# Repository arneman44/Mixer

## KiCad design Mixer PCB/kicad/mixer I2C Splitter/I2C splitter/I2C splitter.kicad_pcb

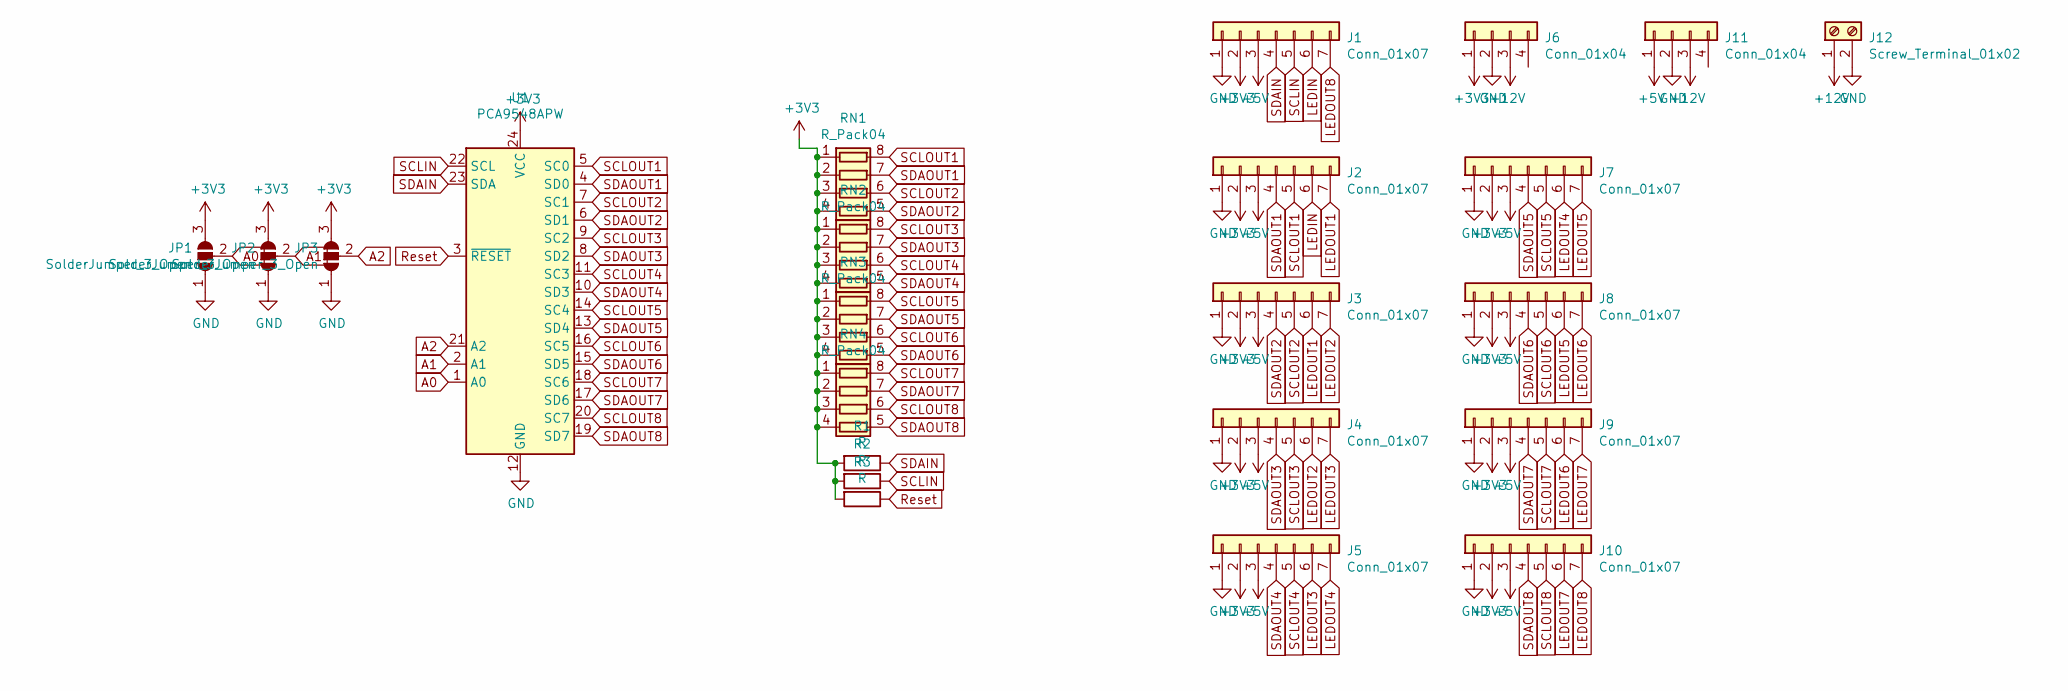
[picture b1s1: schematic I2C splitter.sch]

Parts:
J1, J2, J3, J4, J5, J7, J8, J9, J10: Conn_01x07; PinSocket_1x07_P2.54mm_Vertical
J6, J11: Conn_01x04; PinSocket_1x04_P2.54mm_Vertical
J12: Screw_Terminal_01x02; TerminalBlock_bornier-2_P5.08mm
JP1, JP2, JP3: SolderJumper_3_Open; SolderJumper-3_P1.3mm_Open_RoundedPad1.0x1.5mm
R1, R2, R3: R; R_0805_2012Metric_Pad1.15x1.40mm_HandSolder
RN1, RN2, RN3, RN4: R_Pack04; R_Array_Convex_4x0603
U1: PCA9548APW; TSSOP-24_4.4x7.8mm_P0.65mm

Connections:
+3V3: J1.2, J2.2, J3.2, J4.2, J5.2, J6.1, J7.2, J8.2, J9.2, J10.2, JP1.3 (B), JP2.3 (B), JP3.3 (B), R1.2, R2.2, R3.2, RN1.1 (R1.1), RN1.2 (R2.1), RN1.3 (R3.1), RN1.4 (R4.1), RN2.1 (R1.1), RN2.2 (R2.1), RN2.3 (R3.1), RN2.4 (R4.1), RN3.1 (R1.1), RN3.2 (R2.1), RN3.3 (R3.1), RN3.4 (R4.1), RN4.1 (R1.1), RN4.2 (R2.1), RN4.3 (R3.1), RN4.4 (R4.1), U1.24 (VCC)
+5V: J1.3, J2.3, J3.3, J4.3, J5.3, J7.3, J8.3, J9.3, J10.3, J11.1
+12V: J6.3, J11.3, J12.1
A0: JP1.2 (C), U1.1 (A0)
A1: JP2.2 (C), U1.2 (A1)
A2: JP3.2 (C), U1.21 (A2)
GND: J1.1, J2.1, J3.1, J4.1, J5.1, J6.2, J7.1, J8.1, J9.1, J10.1, J11.2, J12.2, JP1.1 (A), JP2.1 (A), JP3.1 (A), U1.12 (GND)
LEDIN: J1.6, J2.6
LEDOUT1: J2.7, J3.6
LEDOUT2: J3.7, J4.6
LEDOUT3: J4.7, J5.6
LEDOUT4: J5.7, J7.6
LEDOUT5: J7.7, J8.6
LEDOUT6: J8.7, J9.6
LEDOUT7: J9.7, J10.6
LEDOUT8: J1.7, J10.7
Reset: R3.1, U1.3 (~RESET)
SCLIN: J1.5, R2.1, U1.22 (SCL)
SCLOUT1: J2.5, RN1.8 (R1.2), U1.5 (SC0)
SCLOUT2: J3.5, RN1.6 (R3.2), U1.7 (SC1)
SCLOUT3: J4.5, RN2.8 (R1.2), U1.9 (SC2)
SCLOUT4: J5.5, RN2.6 (R3.2), U1.11 (SC3)
SCLOUT5: J7.5, RN3.8 (R1.2), U1.14 (SC4)
SCLOUT6: J8.5, RN3.6 (R3.2), U1.16 (SC5)
SCLOUT7: J9.5, RN4.8 (R1.2), U1.18 (SC6)
SCLOUT8: J10.5, RN4.6 (R3.2), U1.20 (SC7)
SDAIN: J1.4, R1.1, U1.23 (SDA)
SDAOUT1: J2.4, RN1.7 (R2.2), U1.4 (SD0)
SDAOUT2: J3.4, RN1.5 (R4.2), U1.6 (SD1)
SDAOUT3: J4.4, RN2.7 (R2.2), U1.8 (SD2)
SDAOUT4: J5.4, RN2.5 (R4.2), U1.10 (SD3)
SDAOUT5: J7.4, RN3.7 (R2.2), U1.13 (SD4)
SDAOUT6: J8.4, RN3.5 (R4.2), U1.15 (SD5)
SDAOUT7: J9.4, RN4.7 (R2.2), U1.17 (SD6)
SDAOUT8: J10.4, RN4.5 (R4.2), U1.19 (SD7)

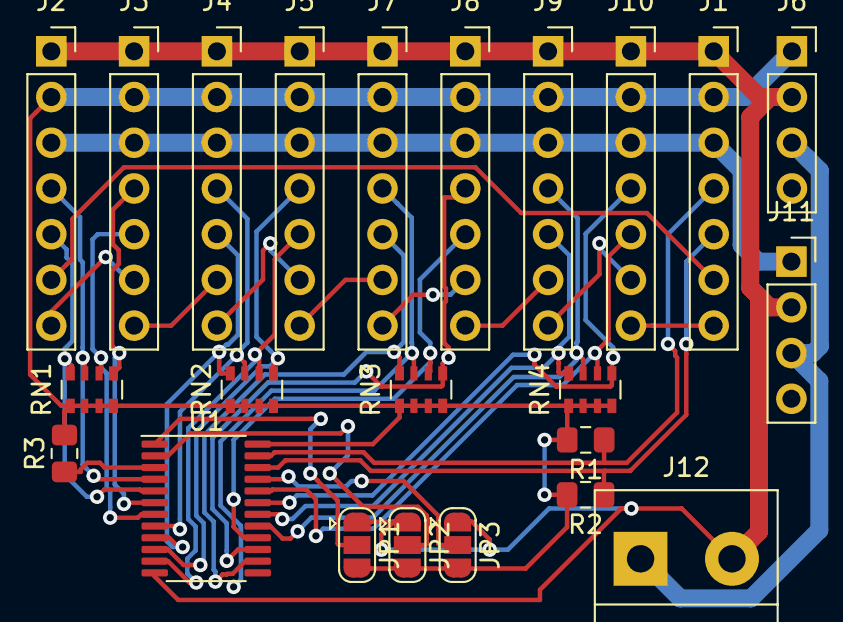
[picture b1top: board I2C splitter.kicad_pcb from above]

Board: 2 copper layers, 23 parts (0 on the bottom side), 35 nets.

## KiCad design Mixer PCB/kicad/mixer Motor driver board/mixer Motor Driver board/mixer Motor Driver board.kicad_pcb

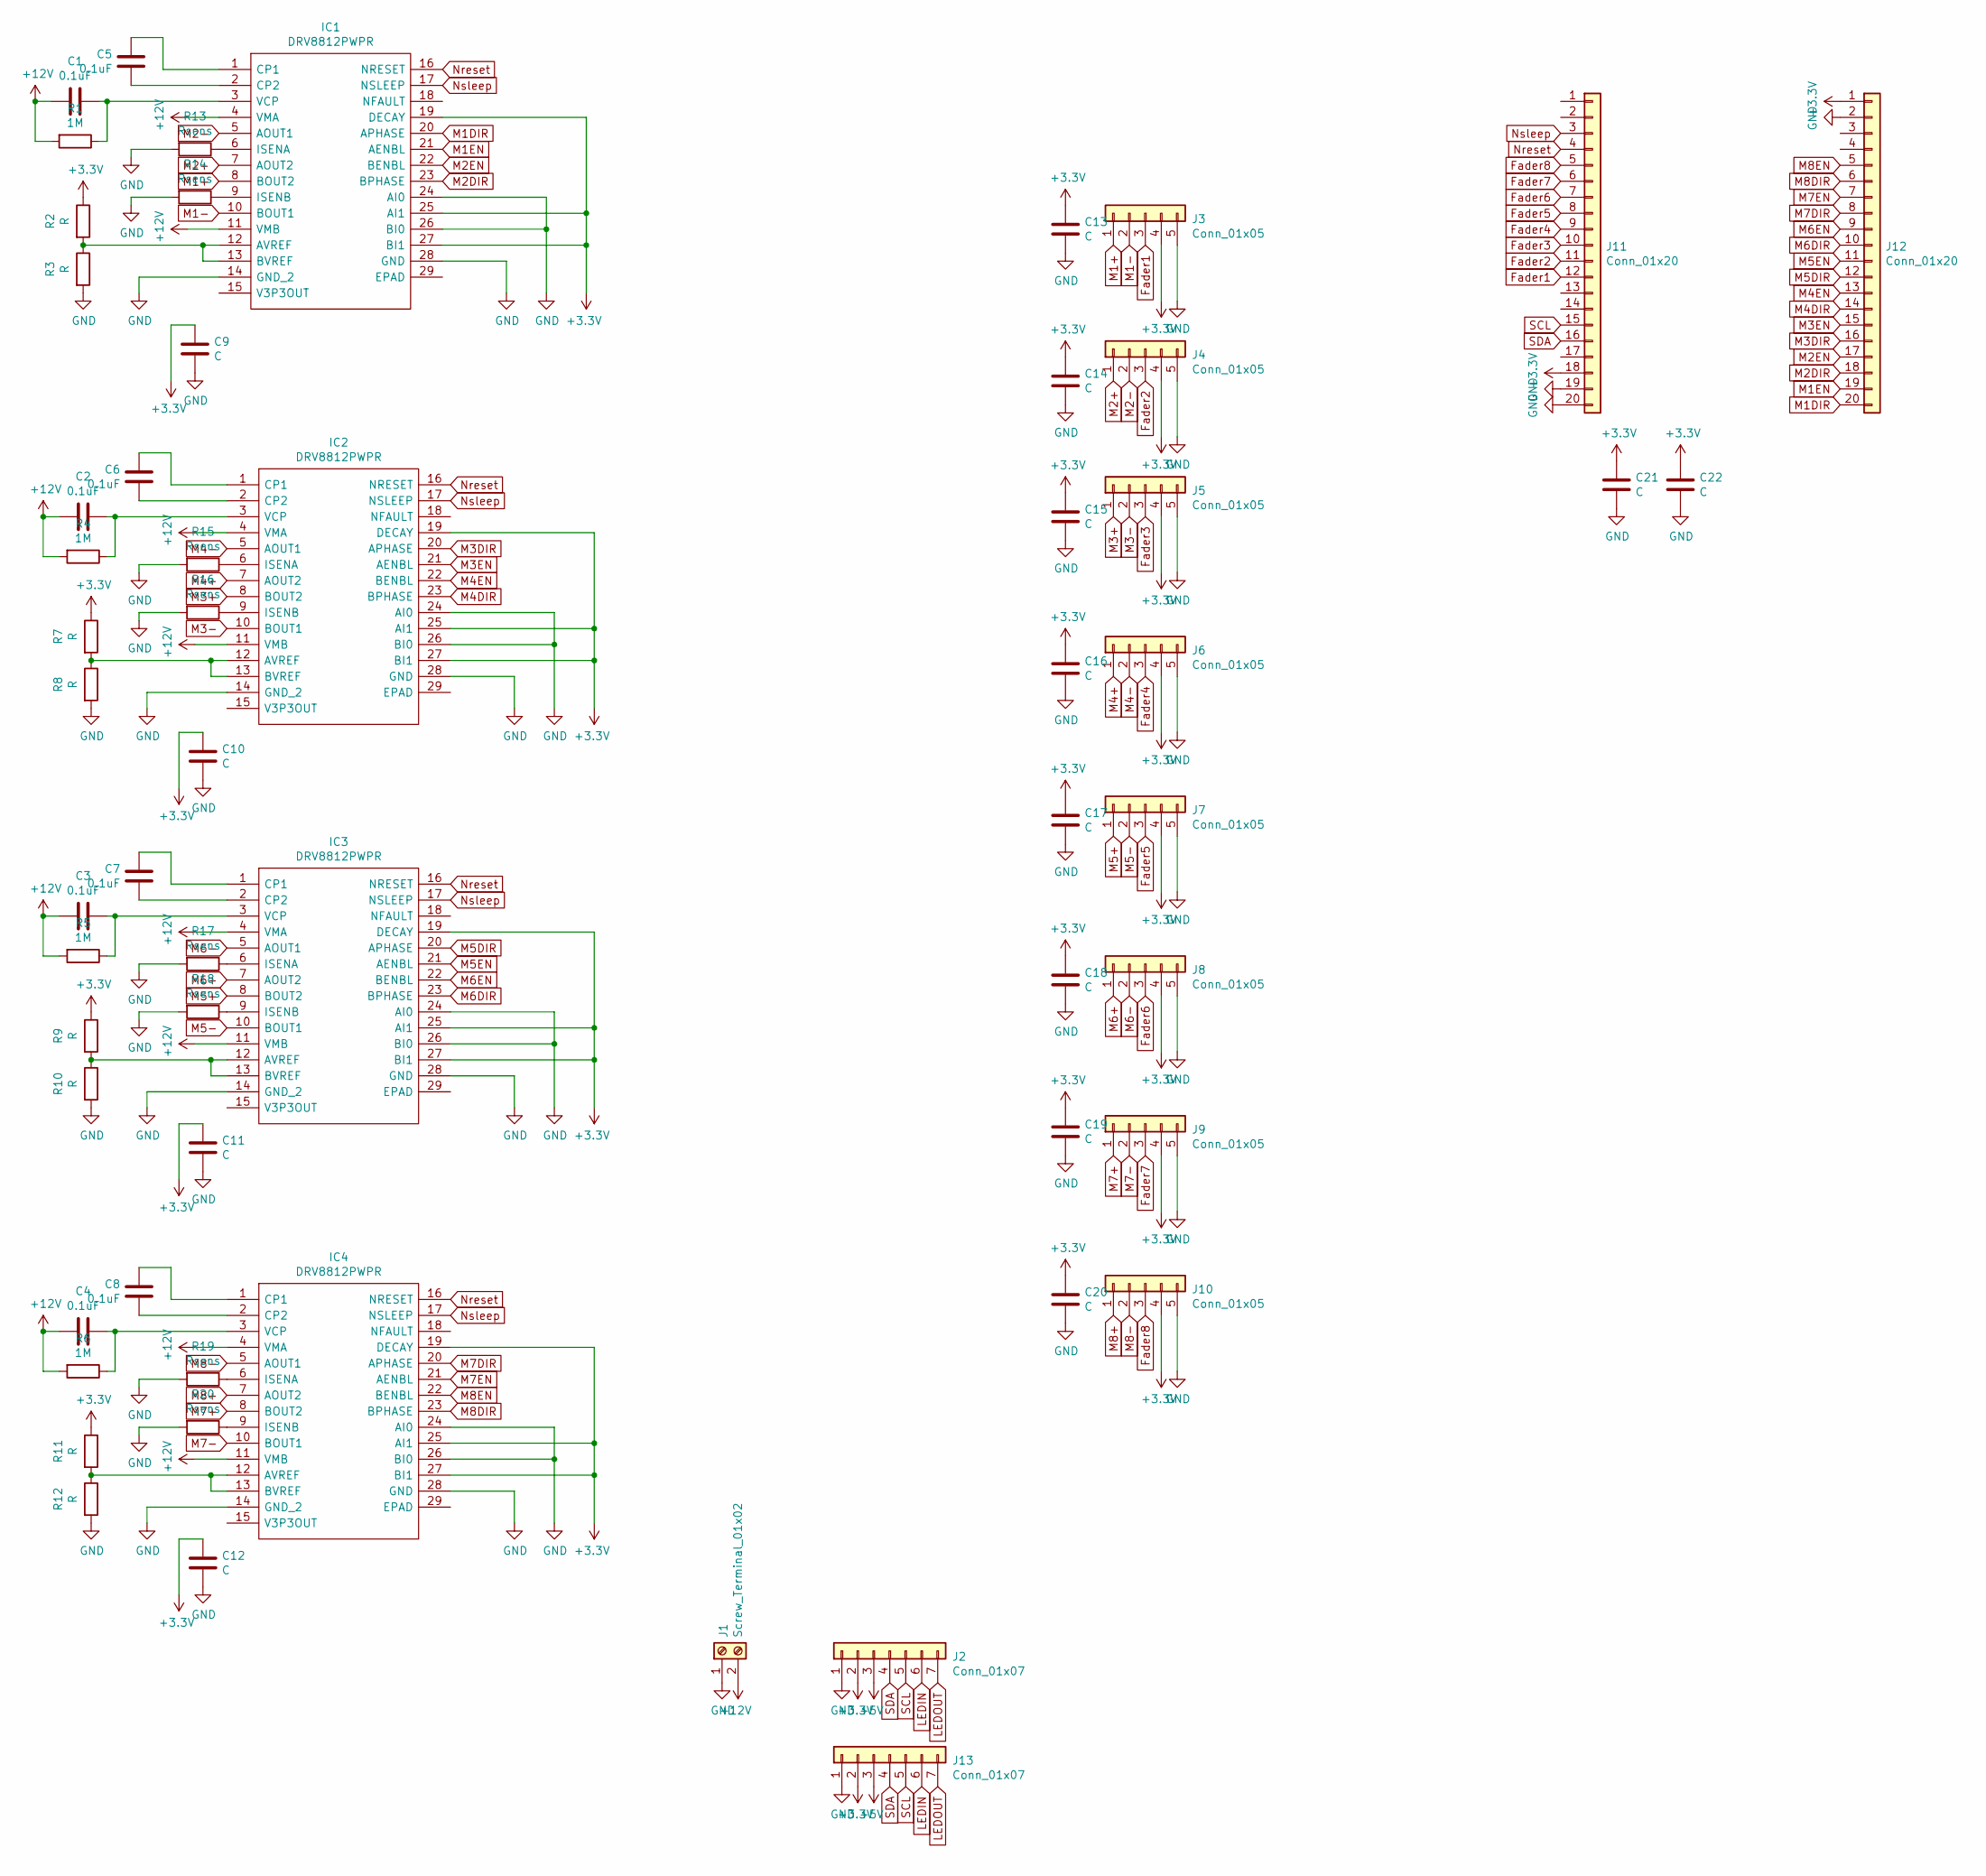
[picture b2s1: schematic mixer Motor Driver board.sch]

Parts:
C1, C2, C3, C4, C5, C6, C7, C8: 0.1uF; C_0805_2012Metric_Pad1.15x1.40mm_HandSolder
C9, C10, C11, C12, C13, C14, C15, C16, C17, C18, C19, C20, C21, C22: C; C_0805_2012Metric_Pad1.15x1.40mm_HandSolder
IC1, IC2, IC3, IC4: DRV8812PWPR; SOP65P640X120-29N; Manufacturer_Part_Number DRV8812PWPR; Mouser Part Number 595-DRV8812PWPR
J1: Screw_Terminal_01x02; TerminalBlock_bornier-2_P5.08mm
J2, J13: Conn_01x07; PinSocket_1x07_P2.54mm_Vertical
J3, J4, J5, J6, J7, J8, J9, J10: Conn_01x05; PinSocket_1x05_P2.54mm_Vertical
J11, J12: Conn_01x20; PinSocket_1x20_P2.54mm_Vertical
R1, R4, R5, R6: 1M; R_0805_2012Metric_Pad1.15x1.40mm_HandSolder
R2, R3, R7, R8, R9, R10, R11, R12: R; R_0805_2012Metric_Pad1.15x1.40mm_HandSolder
R13, R14, R15, R16, R17, R18, R19, R20: Rsens; R_1206_3216Metric_Pad1.42x1.75mm_HandSolder

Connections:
+3V3: C9.1, C10.1, C11.1, C12.1, C13.1, C14.1, C15.1, C16.1, C17.1, C18.1, C19.1, C20.1, C21.1, C22.1, IC1.19 (DECAY), IC1.25 (AI1), IC1.27 (BI1), IC2.19 (DECAY), IC2.25 (AI1), IC2.27 (BI1), IC3.19 (DECAY), IC3.25 (AI1), IC3.27 (BI1), IC4.19 (DECAY), IC4.25 (AI1), IC4.27 (BI1), J2.2, J3.4, J4.4, J5.4, J6.4, J7.4, J8.4, J9.4, J10.4, J11.18, J12.1, J13.2, R2.1, R7.1, R9.1, R11.1
+5V: J2.3, J13.3
+12V: C1.2, C2.2, C3.2, C4.2, IC1.4 (VMA), IC1.11 (VMB), IC2.4 (VMA), IC2.11 (VMB), IC3.4 (VMA), IC3.11 (VMB), IC4.4 (VMA), IC4.11 (VMB), J1.2, R1.2, R4.2, R5.2, R6.2
Fader1: J3.3, J11.12
Fader2: J4.3, J11.11
Fader3: J5.3, J11.10
Fader4: J6.3, J11.9
Fader5: J7.3, J11.8
Fader6: J8.3, J11.7
Fader7: J9.3, J11.6
Fader8: J10.3, J11.5
GND: C9.2, C10.2, C11.2, C12.2, C13.2, C14.2, C15.2, C16.2, C17.2, C18.2, C19.2, C20.2, C21.2, C22.2, IC1.14 (GND_2), IC1.24 (AI0), IC1.26 (BI0), IC1.28 (GND), IC2.14 (GND_2), IC2.24 (AI0), IC2.26 (BI0), IC2.28 (GND), IC3.14 (GND_2), IC3.24 (AI0), IC3.26 (BI0), IC3.28 (GND), IC4.14 (GND_2), IC4.24 (AI0), IC4.26 (BI0), IC4.28 (GND), J1.1, J2.1, J3.5, J4.5, J5.5, J6.5, J7.5, J8.5, J9.5, J10.5, J11.19, J11.20, J12.2, J13.1, R3.2, R8.2, R10.2, R12.2, R13.2, R14.2, R15.2, R16.2, R17.2, R18.2, R19.2, R20.2
LEDIN: J2.6, J13.6
LEDOUT: J2.7, J13.7
M1+: IC1.8 (BOUT2), J3.1
M1-: IC1.10 (BOUT1), J3.2
M1DIR: IC1.20 (APHASE), J12.20
M1EN: IC1.21 (AENBL), J12.19
M2+: IC1.7 (AOUT2), J4.1
M2-: IC1.5 (AOUT1), J4.2
M2DIR: IC1.23 (BPHASE), J12.18
M2EN: IC1.22 (BENBL), J12.17
M3+: IC2.8 (BOUT2), J5.1
M3-: IC2.10 (BOUT1), J5.2
M3DIR: IC2.20 (APHASE), J12.16
M3EN: IC2.21 (AENBL), J12.15
M4+: IC2.7 (AOUT2), J6.1
M4-: IC2.5 (AOUT1), J6.2
M4DIR: IC2.23 (BPHASE), J12.14
M4EN: IC2.22 (BENBL), J12.13
M5+: IC3.8 (BOUT2), J7.1
M5-: IC3.10 (BOUT1), J7.2
M5DIR: IC3.20 (APHASE), J12.12
M5EN: IC3.21 (AENBL), J12.11
M6+: IC3.7 (AOUT2), J8.1
M6-: IC3.5 (AOUT1), J8.2
M6DIR: IC3.23 (BPHASE), J12.10
M6EN: IC3.22 (BENBL), J12.9
M7+: IC4.8 (BOUT2), J9.1
M7-: IC4.10 (BOUT1), J9.2
M7DIR: IC4.20 (APHASE), J12.8
M7EN: IC4.21 (AENBL), J12.7
M8+: IC4.7 (AOUT2), J10.1
M8-: IC4.5 (AOUT1), J10.2
M8DIR: IC4.23 (BPHASE), J12.6
M8EN: IC4.22 (BENBL), J12.5
unnamed: C1.1, IC1.3 (VCP), R1.1
unnamed: C2.1, IC2.3 (VCP), R4.1
unnamed: C3.1, IC3.3 (VCP), R5.1
unnamed: C4.1, IC4.3 (VCP), R6.1
unnamed: C5.1, IC1.2 (CP2)
unnamed: C5.2, IC1.1 (CP1)
unnamed: C6.1, IC2.2 (CP2)
unnamed: C6.2, IC2.1 (CP1)
unnamed: C7.1, IC3.2 (CP2)
unnamed: C7.2, IC3.1 (CP1)
unnamed: C8.1, IC4.2 (CP2)
unnamed: C8.2, IC4.1 (CP1)
unnamed: IC1.6 (ISENA), R13.1
unnamed: IC1.9 (ISENB), R14.1
unnamed: IC1.12 (AVREF), IC1.13 (BVREF), R2.2, R3.1
unnamed: IC2.6 (ISENA), R15.1
unnamed: IC2.9 (ISENB), R16.1
unnamed: IC2.12 (AVREF), IC2.13 (BVREF), R7.2, R8.1
unnamed: IC3.6 (ISENA), R17.1
unnamed: IC3.9 (ISENB), R18.1
unnamed: IC3.12 (AVREF), IC3.13 (BVREF), R9.2, R10.1
unnamed: IC4.6 (ISENA), R19.1
unnamed: IC4.9 (ISENB), R20.1
unnamed: IC4.12 (AVREF), IC4.13 (BVREF), R11.2, R12.1
Nreset: IC1.16 (NRESET), IC2.16 (NRESET), IC3.16 (NRESET), IC4.16 (NRESET), J11.4
Nsleep: IC1.17 (NSLEEP), IC2.17 (NSLEEP), IC3.17 (NSLEEP), IC4.17 (NSLEEP), J11.3
SCL: J2.5, J11.15, J13.5
SDA: J2.4, J11.16, J13.4

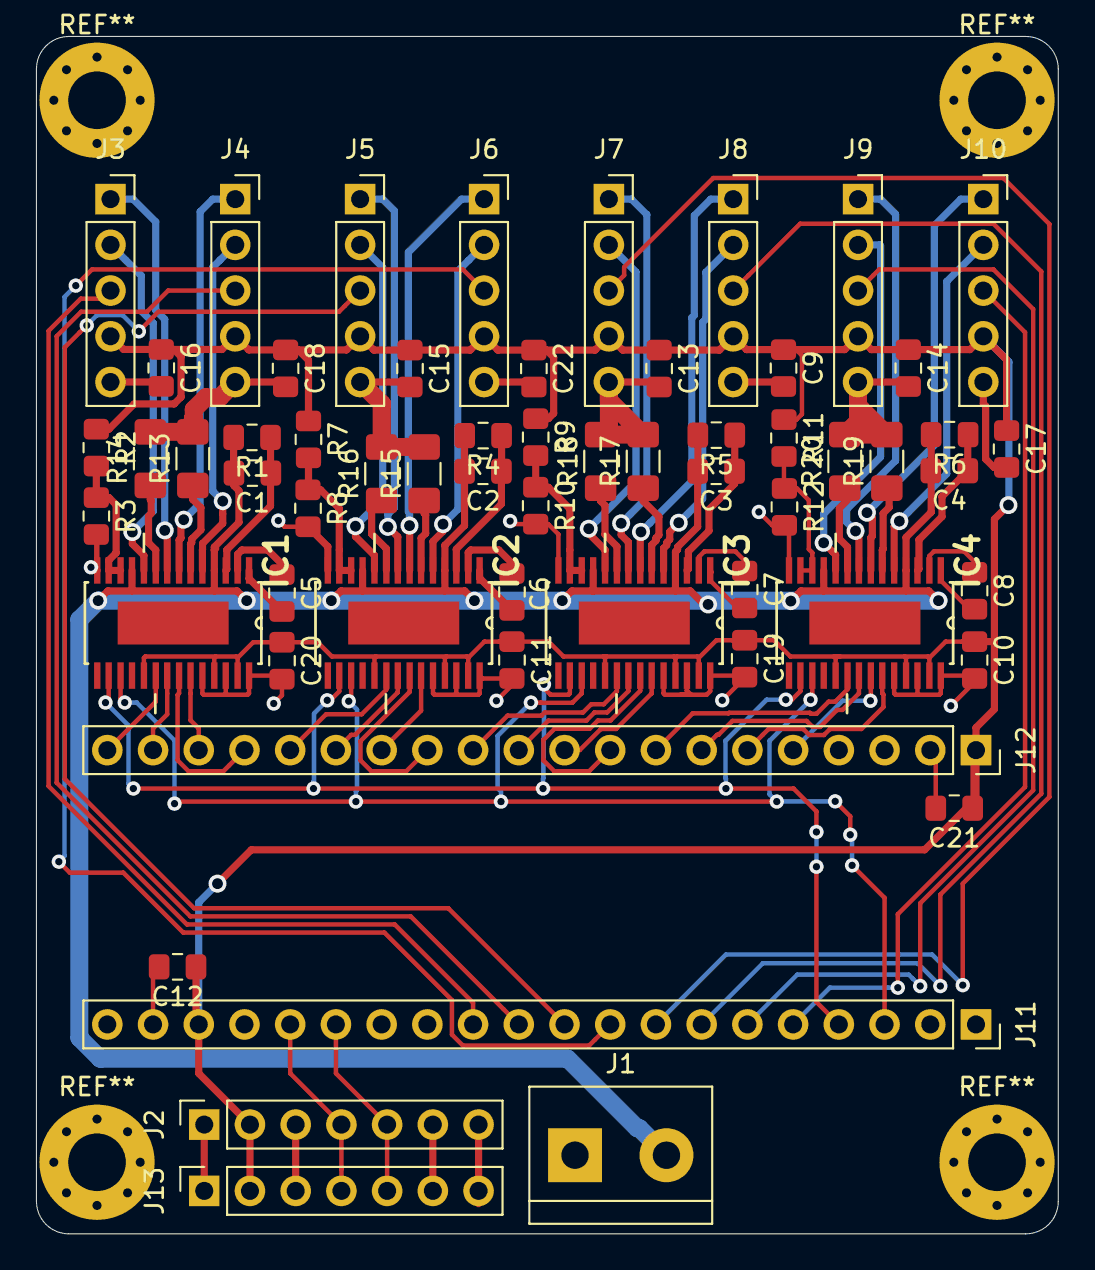
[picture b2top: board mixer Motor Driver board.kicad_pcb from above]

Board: 2 copper layers, 56.8 x 66.5 mm, 59 parts (0 on the bottom side), 74 nets.

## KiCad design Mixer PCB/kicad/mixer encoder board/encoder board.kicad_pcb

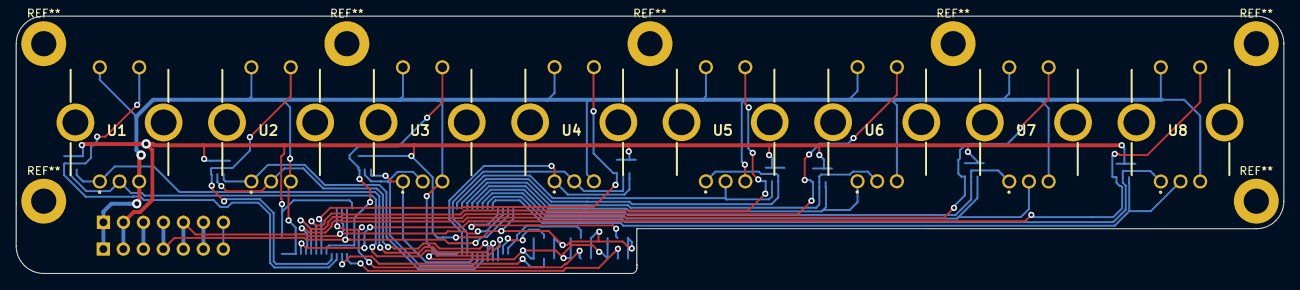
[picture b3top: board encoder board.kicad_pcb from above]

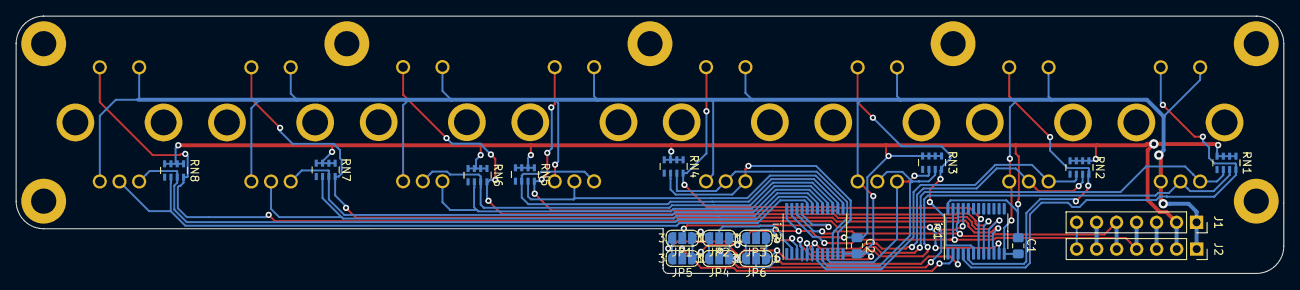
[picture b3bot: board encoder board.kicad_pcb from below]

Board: 2 copper layers, 161.0 x 32.7 mm, 28 parts (20 on the bottom side), 37 nets.

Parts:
C1, C2: C; C_0805_2012Metric_Pad1.15x1.40mm_HandSolder
J1, J2: Conn_01x07; PinSocket_1x07_P2.54mm_Vertical
JP1, JP2, JP3, JP4, JP5, JP6: SolderJumper_3_Open; SolderJumper-3_P1.3mm_Open_RoundedPad1.0x1.5mm_NumberLabels
RN1, RN2, RN3, RN4, RN5, RN6, RN7, RN8: R_Pack04; R_Array_Concave_4x0603
U1, U2, U3, U4, U5, U6, U7, U8: PEC11R-4015F-S0024; PEC12R-4XXXF-SXXXX_1
ic1, ic2: PCA9555; TSSOP-24_4.4x7.8mm_P0.65mm

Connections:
+3V3: C1.1, C2.1, J1.2, J2.2, JP1.3, JP2.3, JP3.3, JP4.3, JP5.3, JP6.3, RN1.1, RN1.2, RN1.3, RN1.4, RN2.1, RN2.2, RN2.3, RN2.4, RN3.1, RN3.2, RN3.3, RN3.4, RN4.1, RN4.2, RN4.3, RN4.4, RN5.1, RN5.2, RN5.3, RN5.4, RN6.1, RN6.2, RN6.3, RN6.4, RN7.1, RN7.2, RN7.3, RN7.4, RN8.1, RN8.2, RN8.3, RN8.4, ic1.24, ic2.24
+5V: J1.3, J2.3
A0_I2C1: JP4.2, ic1.21
A0_I2C2: JP1.2, ic2.21
A1_I2C1: JP5.2, ic1.2
A1_I2C2: JP2.2, ic2.2
A2_I2C1: JP6.2, ic1.3
A2_I2C2: JP3.2, ic2.3
Encoder1A: RN1.6, U1.1, ic2.5
Encoder1B: RN1.7, U1.3, ic2.4
Encoder1Button: RN1.8, U1.5, ic1.4
Encoder2A: RN2.6, U2.1, ic2.7
Encoder2B: RN2.7, U2.3, ic2.6
Encoder2Button: RN2.8, U2.5, ic1.5
Encoder3A: RN3.6, U3.1, ic2.9
Encoder3B: RN3.7, U3.3, ic2.8
Encoder3Button: RN3.8, U3.5, ic1.6
Encoder4A: RN4.6, U4.1, ic2.11
Encoder4B: RN4.7, U4.3, ic2.10
Encoder4Button: RN4.8, U4.5, ic1.7
Encoder5A: RN5.6, U5.1, ic2.14
Encoder5B: RN5.7, U5.3, ic2.13
Encoder5Button: RN5.8, U5.5, ic1.8
Encoder6A: RN6.6, U6.1, ic2.16
Encoder6B: RN6.7, U6.3, ic2.15
Encoder6Button: RN6.8, U6.5, ic1.9
Encoder7A: RN7.7, U7.1, ic2.17
Encoder7B: RN7.6, U7.3, ic2.18
Encoder7Button: RN7.8, U7.5, ic1.10
Encoder8A: RN8.7, U8.1, ic2.19
Encoder8B: RN8.6, U8.3, ic2.20
Encoder8Button: RN8.8, U8.5, ic1.11
GND: C1.2, C2.2, J1.1, J2.1, JP1.1, JP2.1, JP3.1, JP4.1, JP5.1, JP6.1, U1.2, U1.4, U2.2, U2.4, U3.2, U3.4, U4.2, U4.4, U5.2, U5.4, U6.2, U6.4, U7.2, U7.4, U8.2, U8.4, ic1.12, ic2.12
LEDIN: J1.6, J2.6
LEDOUT1: J1.7, J2.7
SCL: J1.5, J2.5, ic1.22, ic2.22
SDA: J1.4, J2.4, ic1.23, ic2.23

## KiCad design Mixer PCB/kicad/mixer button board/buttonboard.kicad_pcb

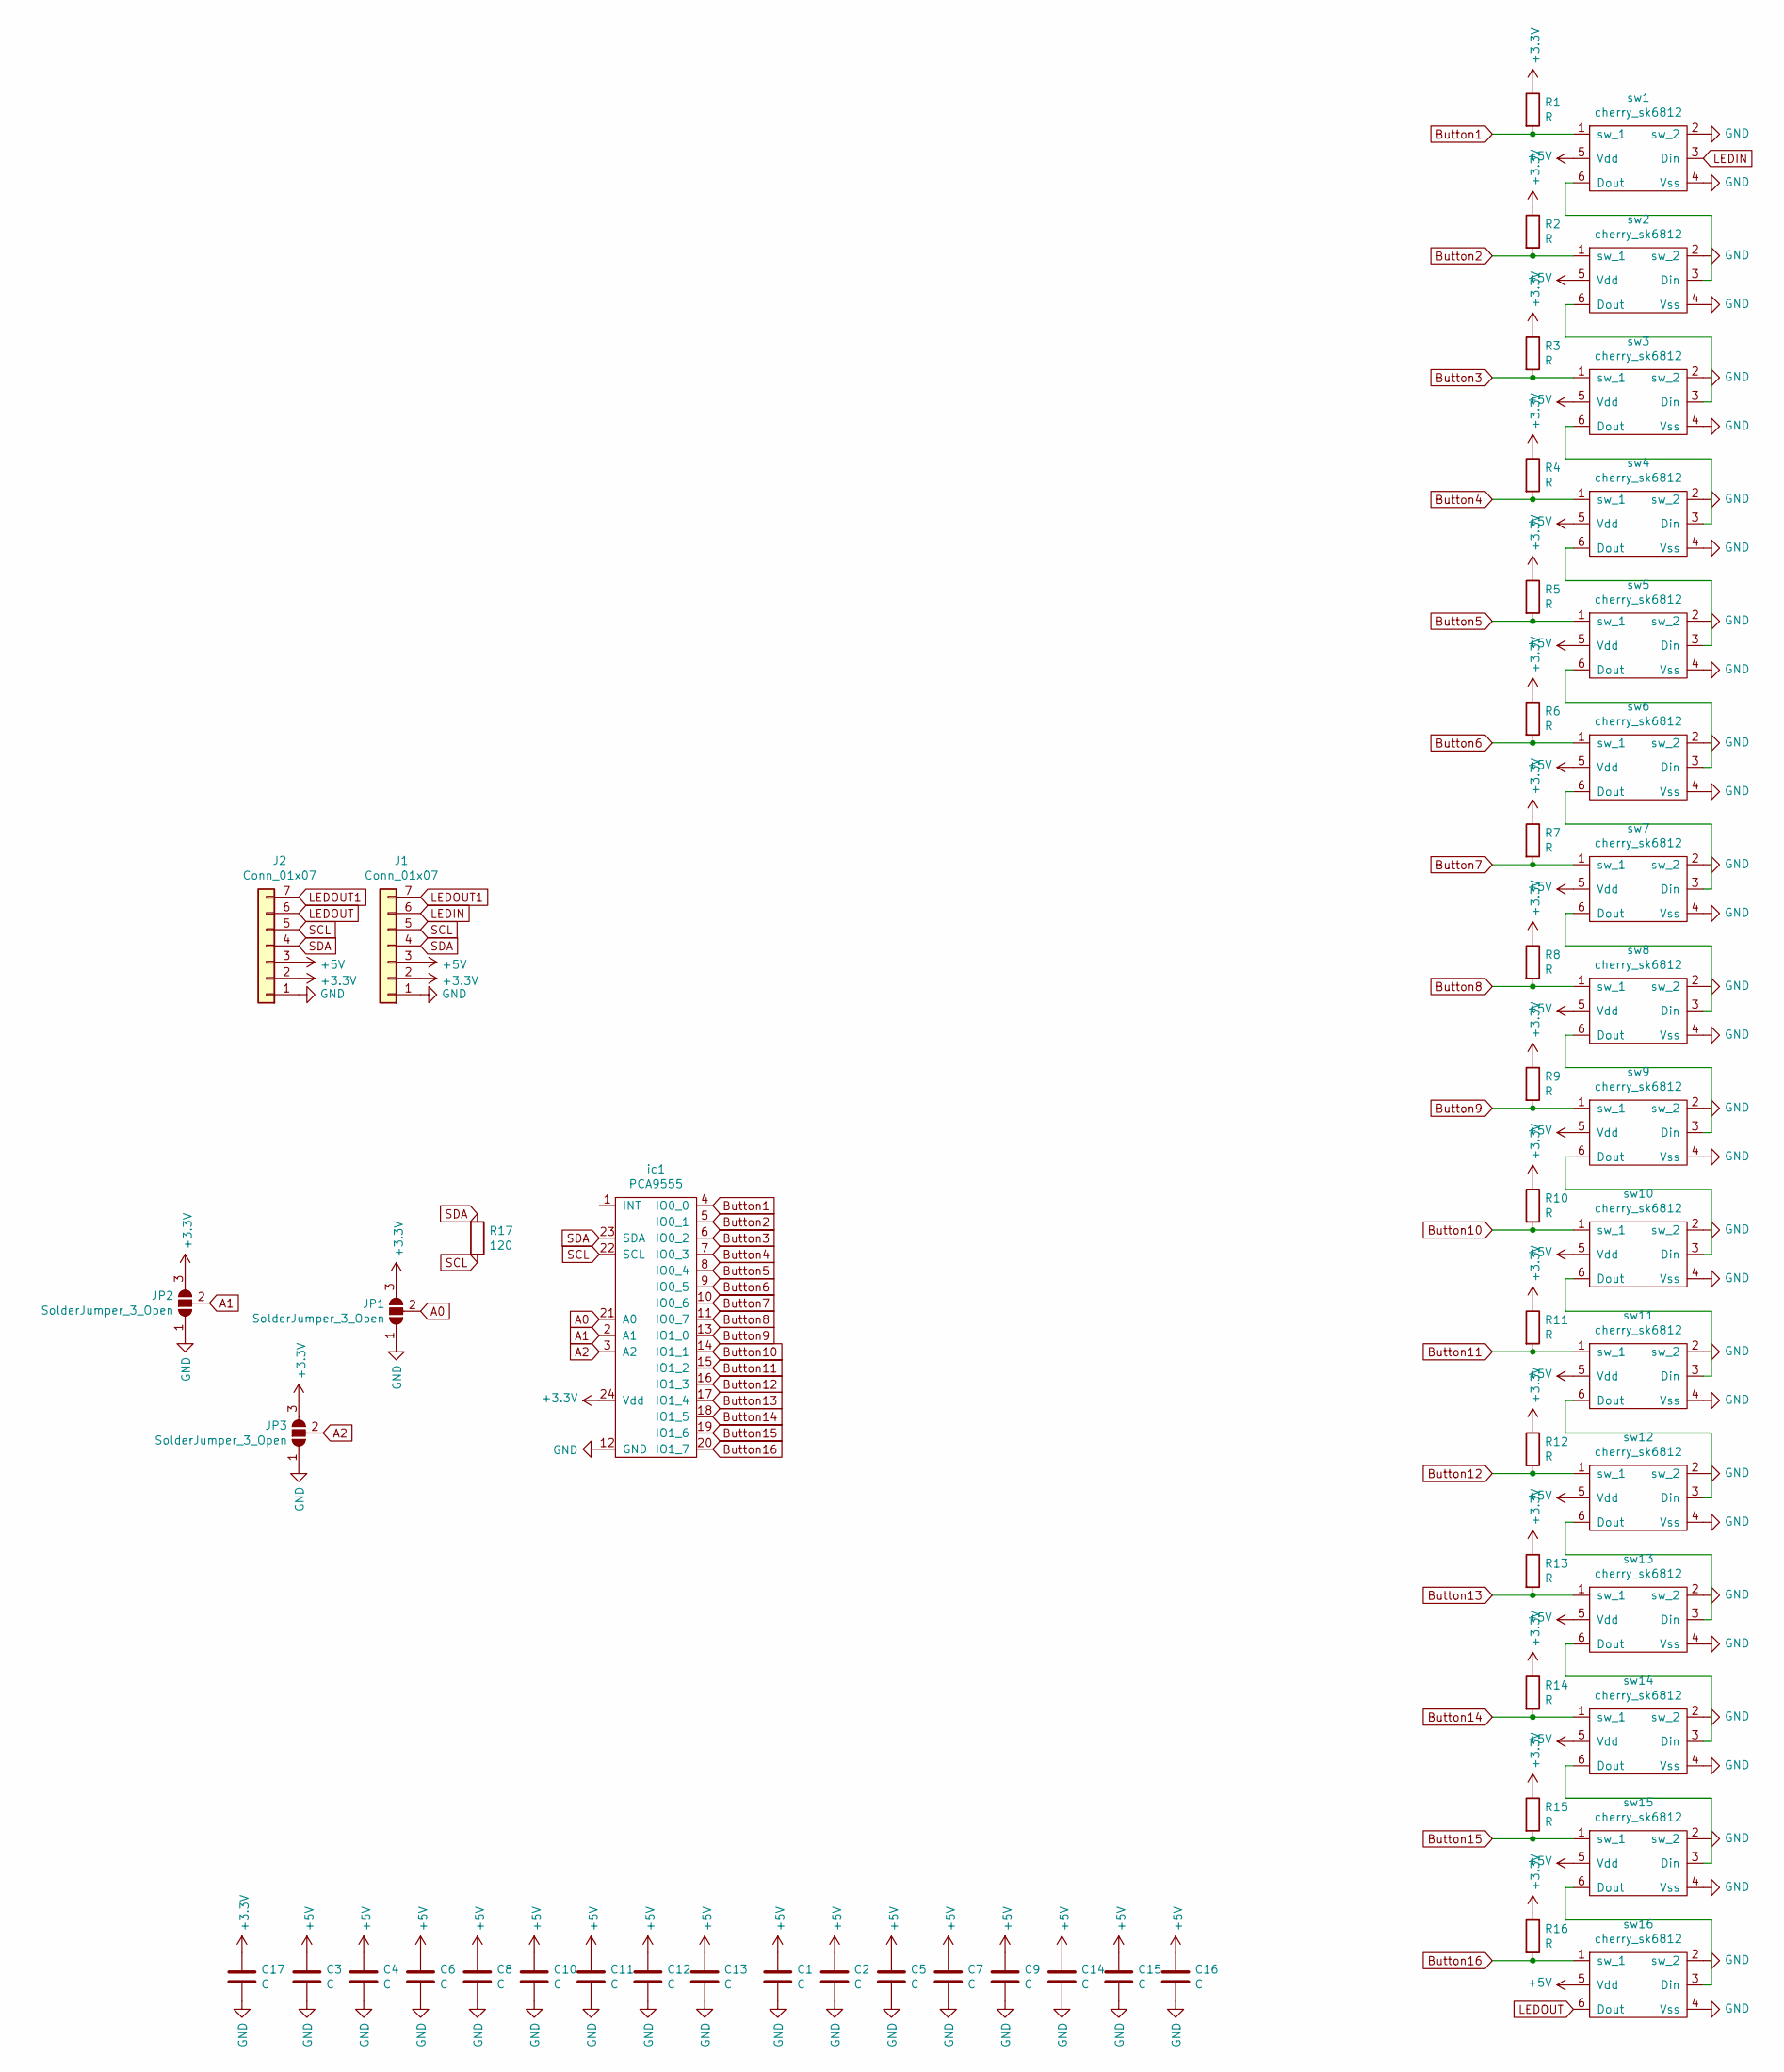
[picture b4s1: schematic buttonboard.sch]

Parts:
C1, C2, C3, C4, C5, C6, C7, C8, C9, C10, C11, C12, C13, C14, C15, C16, C17: C; C_0805_2012Metric_Pad1.15x1.40mm_HandSolder
J1, J2: Conn_01x07; PinSocket_1x07_P2.54mm_Vertical
JP1, JP2, JP3: SolderJumper_3_Open; SolderJumper-3_P1.3mm_Open_RoundedPad1.0x1.5mm
R1, R2, R3, R4, R5, R6, R7, R8, R9, R10, R11, R12, R13, R14, R15, R16: R; R_0805_2012Metric_Pad1.15x1.40mm_HandSolder
R17: 120; R_0805_2012Metric_Pad1.15x1.40mm_HandSolder
ic1: PCA9555; TSSOP-24_4.4x7.8mm_P0.65mm
sw1, sw2, sw3, sw4, sw5, sw6, sw7, sw8, sw9, sw10, sw11, sw12, sw13, sw14, sw15, sw16: cherry_sk6812; Cherry_MX_SK6812_BS

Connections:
+3V3: C17.1, J1.2, J2.2, JP1.3 (B), JP2.3 (B), JP3.3 (B), R1.1, R2.1, R3.1, R4.1, R5.1, R6.1, R7.1, R8.1, R9.1, R10.1, R11.1, R12.1, R13.1, R14.1, R15.1, R16.1, ic1.24 (Vdd)
+5V: C1.1, C2.1, C3.1, C4.1, C5.1, C6.1, C7.1, C8.1, C9.1, C10.1, C11.1, C12.1, C13.1, C14.1, C15.1, C16.1, J1.3, J2.3, sw1.5 (Vdd), sw2.5 (Vdd), sw3.5 (Vdd), sw4.5 (Vdd), sw5.5 (Vdd), sw6.5 (Vdd), sw7.5 (Vdd), sw8.5 (Vdd), sw9.5 (Vdd), sw10.5 (Vdd), sw11.5 (Vdd), sw12.5 (Vdd), sw13.5 (Vdd), sw14.5 (Vdd), sw15.5 (Vdd), sw16.5 (Vdd)
A0: JP1.2 (C), ic1.21 (A0)
A1: JP2.2 (C), ic1.2 (A1)
A2: JP3.2 (C), ic1.3 (A2)
Button1: R1.2, ic1.4 (IO0_0), sw1.1 (sw_1)
Button2: R2.2, ic1.5 (IO0_1), sw2.1 (sw_1)
Button3: R3.2, ic1.6 (IO0_2), sw3.1 (sw_1)
Button4: R4.2, ic1.7 (IO0_3), sw4.1 (sw_1)
Button5: R5.2, ic1.8 (IO0_4), sw5.1 (sw_1)
Button6: R6.2, ic1.9 (IO0_5), sw6.1 (sw_1)
Button7: R7.2, ic1.10 (IO0_6), sw7.1 (sw_1)
Button8: R8.2, ic1.11 (IO0_7), sw8.1 (sw_1)
Button9: R9.2, ic1.13 (IO1_0), sw9.1 (sw_1)
Button10: R10.2, ic1.14 (IO1_1), sw10.1 (sw_1)
Button11: R11.2, ic1.15 (IO1_2), sw11.1 (sw_1)
Button12: R12.2, ic1.16 (IO1_3), sw12.1 (sw_1)
Button13: R13.2, ic1.17 (IO1_4), sw13.1 (sw_1)
Button14: R14.2, ic1.18 (IO1_5), sw14.1 (sw_1)
Button15: R15.2, ic1.19 (IO1_6), sw15.1 (sw_1)
Button16: R16.2, ic1.20 (IO1_7), sw16.1 (sw_1)
GND: C1.2, C2.2, C3.2, C4.2, C5.2, C6.2, C7.2, C8.2, C9.2, C10.2, C11.2, C12.2, C13.2, C14.2, C15.2, C16.2, C17.2, J1.1, J2.1, JP1.1 (A), JP2.1 (A), JP3.1 (A), ic1.12 (GND), sw1.2 (sw_2), sw1.4 (Vss), sw2.2 (sw_2), sw2.4 (Vss), sw3.2 (sw_2), sw3.4 (Vss), sw4.2 (sw_2), sw4.4 (Vss), sw5.2 (sw_2), sw5.4 (Vss), sw6.2 (sw_2), sw6.4 (Vss), sw7.2 (sw_2), sw7.4 (Vss), sw8.2 (sw_2), sw8.4 (Vss), sw9.2 (sw_2), sw9.4 (Vss), sw10.2 (sw_2), sw10.4 (Vss), sw11.2 (sw_2), sw11.4 (Vss), sw12.2 (sw_2), sw12.4 (Vss), sw13.2 (sw_2), sw13.4 (Vss), sw14.2 (sw_2), sw14.4 (Vss), sw15.2 (sw_2), sw15.4 (Vss), sw16.2 (sw_2), sw16.4 (Vss)
LEDIN: J1.6, sw1.3 (Din)
LEDOUT: J2.6, sw16.6 (Dout)
LEDOUT1: J1.7, J2.7
unnamed: sw1.6 (Dout), sw2.3 (Din)
unnamed: sw2.6 (Dout), sw3.3 (Din)
unnamed: sw3.6 (Dout), sw4.3 (Din)
unnamed: sw4.6 (Dout), sw5.3 (Din)
unnamed: sw5.6 (Dout), sw6.3 (Din)
unnamed: sw6.6 (Dout), sw7.3 (Din)
unnamed: sw7.6 (Dout), sw8.3 (Din)
unnamed: sw8.6 (Dout), sw9.3 (Din)
unnamed: sw9.6 (Dout), sw10.3 (Din)
unnamed: sw10.6 (Dout), sw11.3 (Din)
unnamed: sw11.6 (Dout), sw12.3 (Din)
unnamed: sw12.6 (Dout), sw13.3 (Din)
unnamed: sw13.6 (Dout), sw14.3 (Din)
unnamed: sw14.6 (Dout), sw15.3 (Din)
unnamed: sw15.6 (Dout), sw16.3 (Din)
SCL: J1.5, J2.5, R17.2, ic1.22 (SCL)
SDA: J1.4, J2.4, R17.1, ic1.23 (SDA)

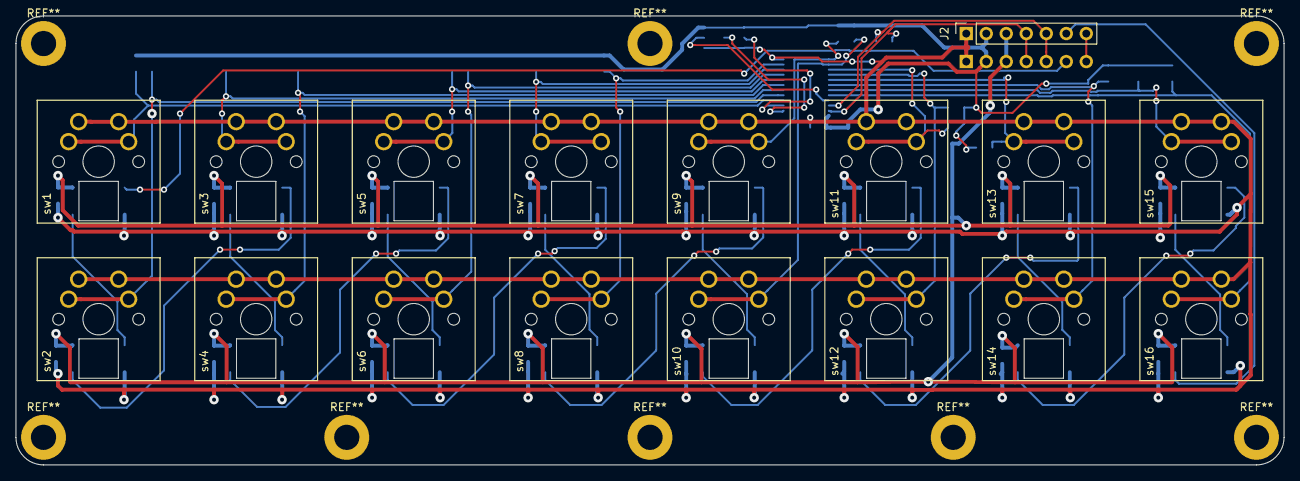
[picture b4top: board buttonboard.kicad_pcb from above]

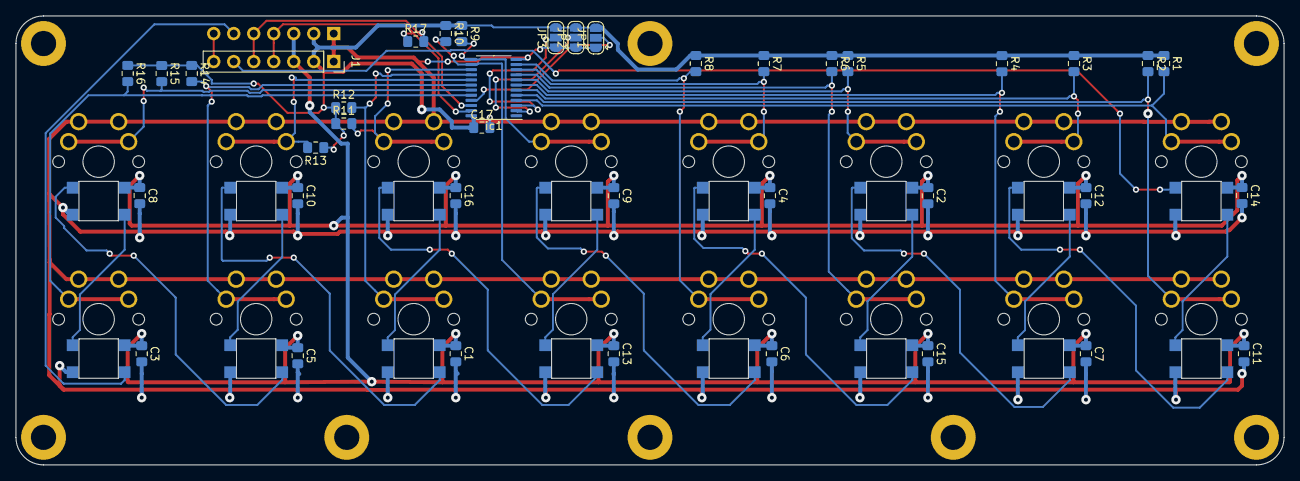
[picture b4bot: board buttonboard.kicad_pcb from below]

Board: 2 copper layers, 161.0 x 57.0 mm, 56 parts (39 on the bottom side), 42 nets.
